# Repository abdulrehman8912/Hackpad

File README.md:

# Hackpad
This is a hackpad with naruto images it got 1 0.91inch screen 1 rotary and a 3x3 layout with mx switches 
How i sued ai i used ai to help debug the errors the problem in kicad and some code 
 Componets:
 Arduino pro micro x1
 mx switches x9
 0.91inch oled screen x1
 rotary x1
 conn x1x6 x2
 conn 1x3 x1 
 Diode 

 software:
 vscode
 fusion 360
 kicad
 QMK

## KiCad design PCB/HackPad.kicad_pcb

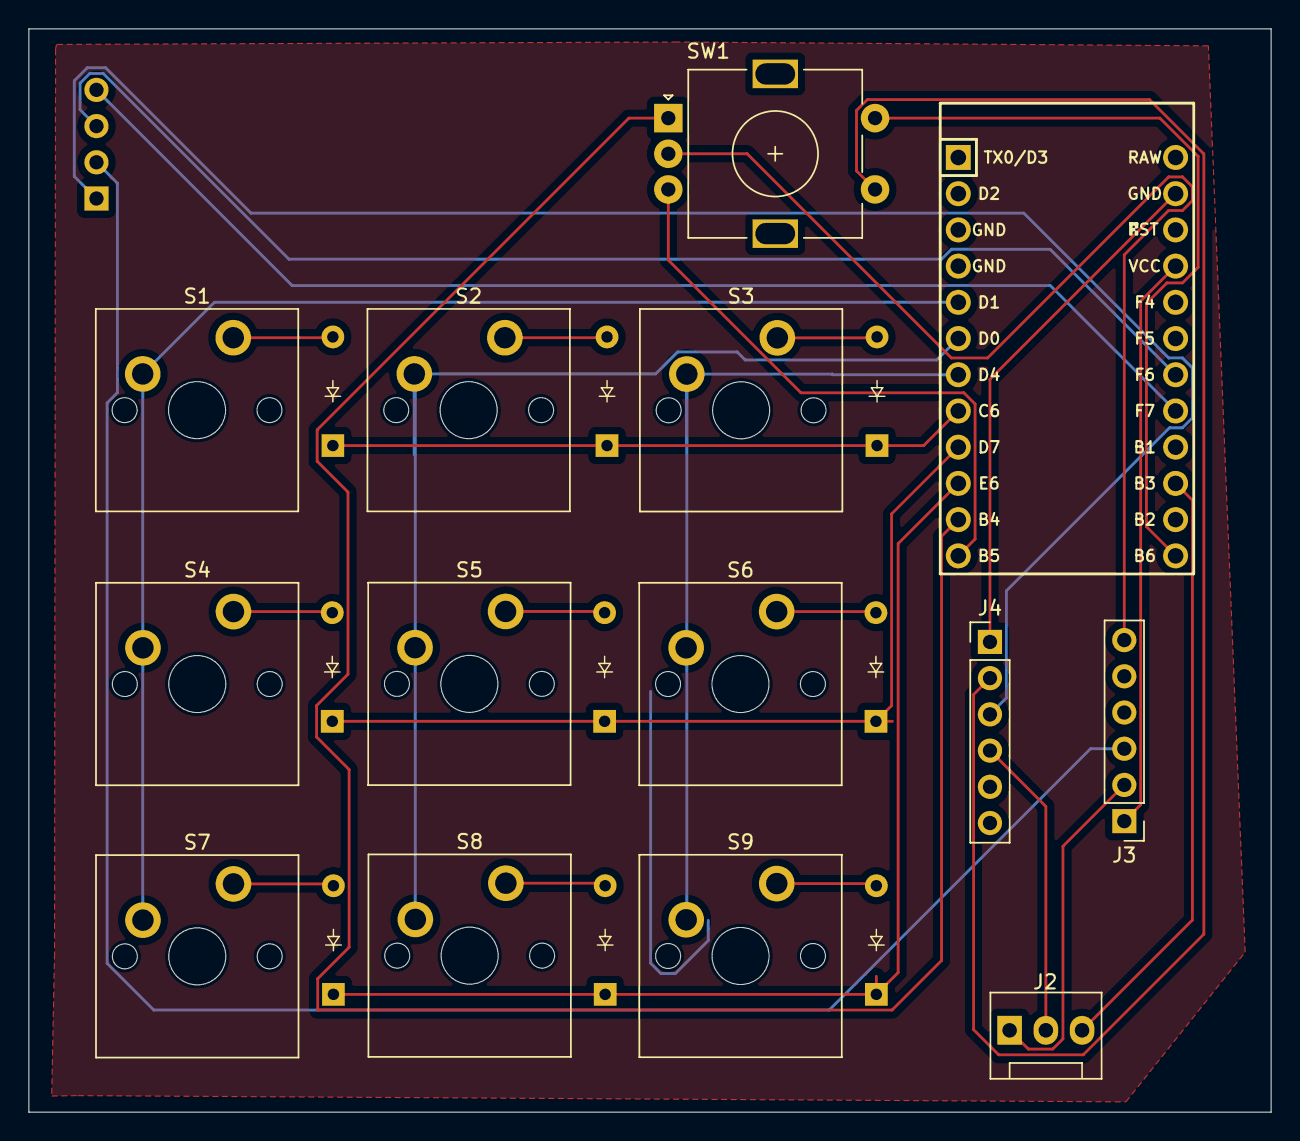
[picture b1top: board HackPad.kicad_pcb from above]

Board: 2 copper layers, 87.1 x 76.0 mm, 24 parts (0 on the bottom side), 29 nets.

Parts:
D1, D2, D3, D4, D5, D6, D7, D8, D9: Diode_DO-35
J1: OLED_128x32
J2: Conn_01x03; FanPinHeader_1x03_P2.54mm_Vertical
J3, J4: Conn_01x06; PinHeader_1x06_P2.54mm_Vertical
S1, S2, S3, S4, S5, S6, S7, S8, S9: MX_PCB_1.00u
SW1: RotaryEncoder_Switch; RotaryEncoder_Alps_EC11E-Switch_Vertical_H20mm
U1: Arduino_Pro_Micro

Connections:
Column 0: S1.1, S4.1, S7.1, U1.5 (2/PD1)
Column 1: S2.1, S5.1, S8.1, U1.6 (3/PD0)
Column 2: S3.1, S6.1, S9.1, U1.7 (4/PD4)
GND: J4.1, U1.23 (GND)
unnamed: D1.2 (A), S1.2
unnamed: D2.2 (A), S2.2
unnamed: D3.2 (A), S3.2
unnamed: D4.2 (A), S4.2
unnamed: D5.2 (A), S5.2
unnamed: D6.2 (A), S6.2
unnamed: D7.2 (A), S7.2
unnamed: D8.2 (A), S8.2
unnamed: D9.2 (A), S9.2
unnamed: J1.1 (GND), J4.3
unnamed: J1.3 (SCL), U1.18 (A1/PF6)
unnamed: J1.4 (SDA), U1.17 (A0/PF7)
unnamed: J1.2 (VCC), J3.3
unnamed: J2.1, J3.2
unnamed: J2.2, J4.4
unnamed: J2.3, U1.15 (14/PB3)
unnamed: J3.6, SW1.C
unnamed: J4.2, SW1.S1
unnamed: SW1.A, U1.11 (8/PB4)
unnamed: SW1.B, U1.12 (9/PB5)
unnamed: SW1.S2, U1.13 (10/PB6)
Row 0: D1.1 (K), D2.1 (K), D3.1 (K), U1.8 (5/PC6)
Row 1: D4.1 (K), D5.1 (K), D6.1 (K), U1.9 (6/PD7)
Row 2: D7.1 (K), D8.1 (K), D9.1 (K), U1.10 (7/PE6)
VCC: J3.1, U1.21 (VCC)
